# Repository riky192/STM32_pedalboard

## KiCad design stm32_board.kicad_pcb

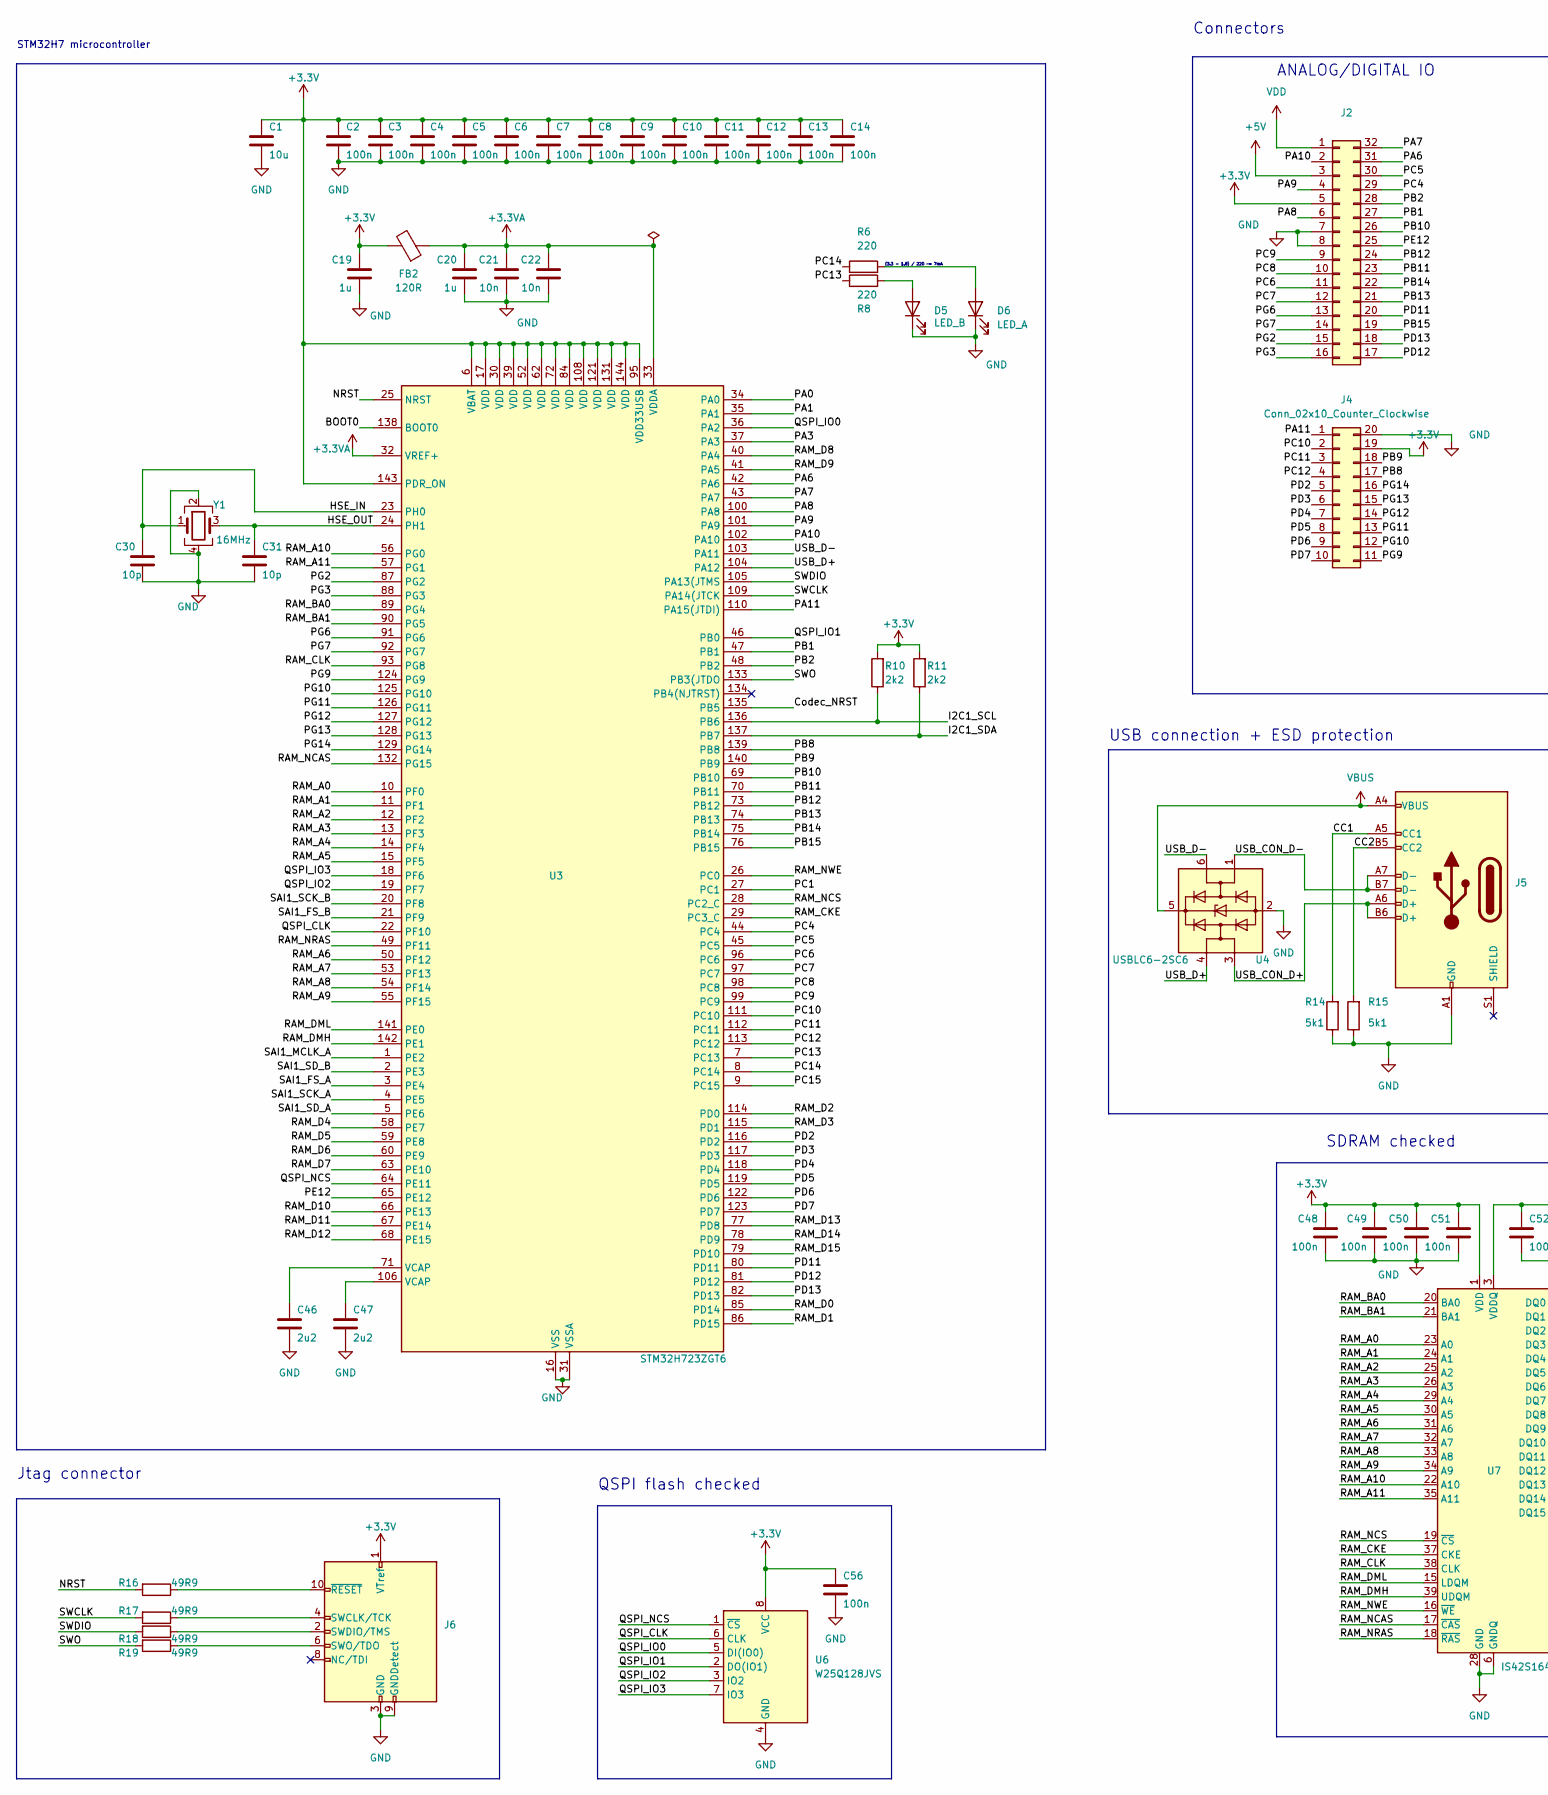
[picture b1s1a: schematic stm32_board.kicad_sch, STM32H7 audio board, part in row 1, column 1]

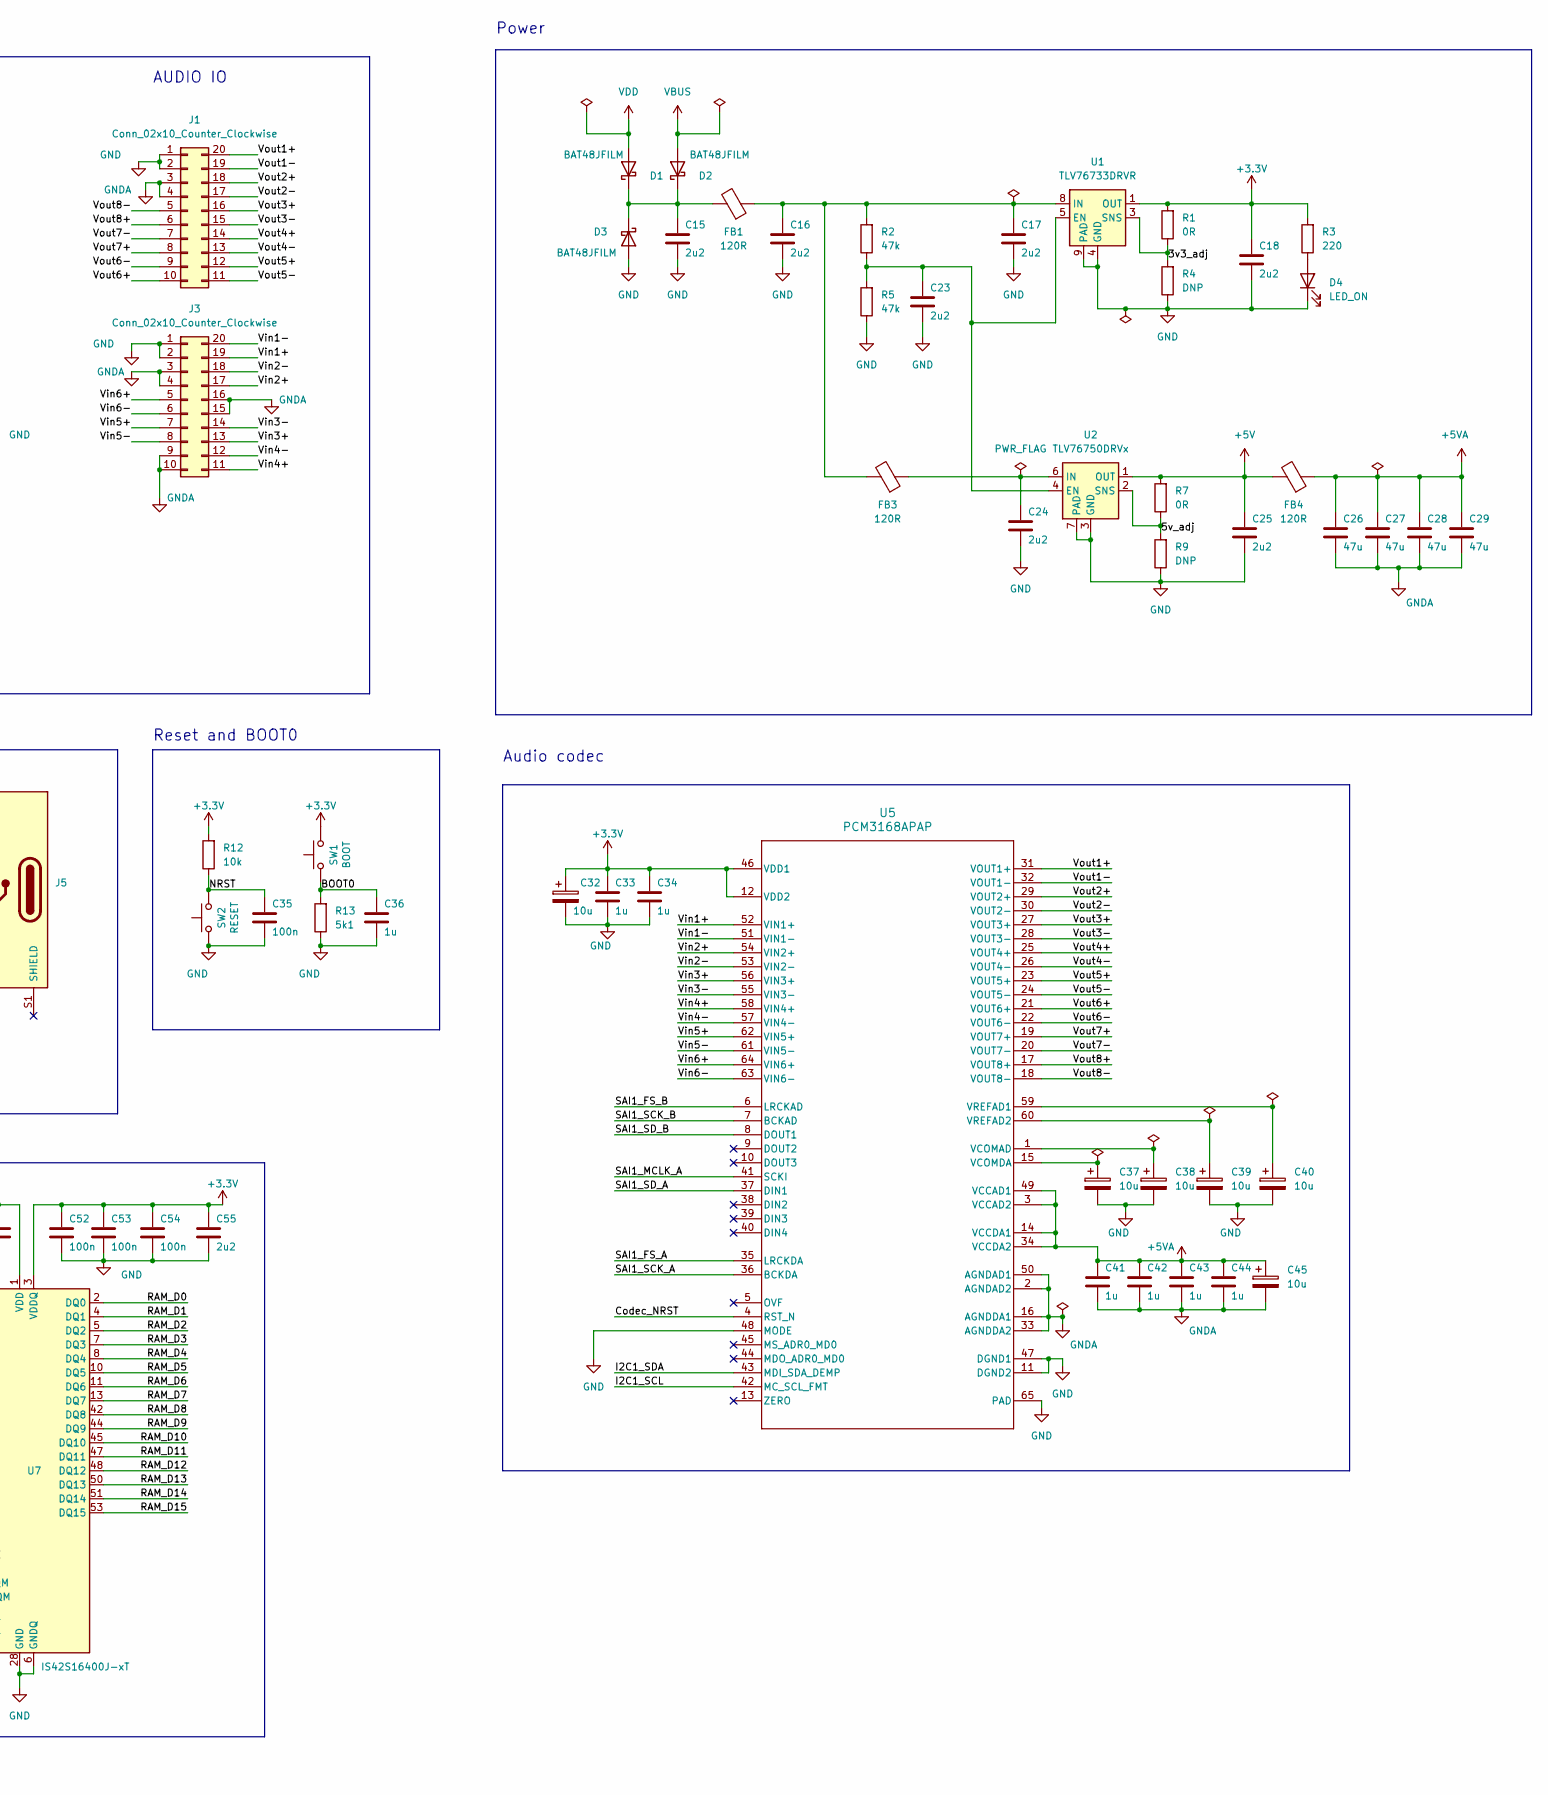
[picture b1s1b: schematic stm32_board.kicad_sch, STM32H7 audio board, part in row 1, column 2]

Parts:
C1, C32, C37, C38, C39, C40, C45: 10u; C_0603_1608Metric_Pad1.08x0.95mm_HandSolder; MANUFACTURER_PART_NUMBER C19702
C2, C3, C4, C5, C6, C7, C8, C9, C10, C11, C12, C13, C14, C35, C48, C49, C50, C51, C52, C53, C54, C56: 100n; C_0603_1608Metric_Pad1.08x0.95mm_HandSolder; MANUFACTURER_PART_NUMBER C14663
C15, C16, C17, C18, C23, C24, C25, C46, C47, C55: 2u2; C_1206_3216Metric_Pad1.33x1.80mm_HandSolder; MANUFACTURER_PART_NUMBER C50254
C19, C20, C33, C34, C36, C41, C42, C43, C44: 1u; C_0603_1608Metric_Pad1.08x0.95mm_HandSolder; MANUFACTURER_PART_NUMBER C15849
C21, C22: 10n; C_0603_1608Metric_Pad1.08x0.95mm_HandSolder; MANUFACTURER_PART_NUMBER C57112
C26, C27, C28, C29: 47u; C_0805_2012Metric_Pad1.18x1.45mm_HandSolder; MANUFACTURER_PART_NUMBER C45783
C30, C31: 10p; C_0603_1608Metric_Pad1.08x0.95mm_HandSolder; MANUFACTURER_PART_NUMBER C1634
D1, D2, D3: BAT48JFILM; D_SOD-323; MANUFACTURER_PART_NUMBER C191023
D4: LED_ON; LED_0805_2012Metric_Pad1.15x1.40mm_HandSolder; MANUFACTURER_PART_NUMBER C2296
D5: LED_B; LED_0805_2012Metric_Pad1.15x1.40mm_HandSolder; MANUFACTURER_PART_NUMBER C5879378
D6: LED_A; LED_0805_2012Metric_Pad1.15x1.40mm_HandSolder; MANUFACTURER_PART_NUMBER C5879378
FB1, FB2, FB3, FB4: 120R; L_0805_2012Metric_Pad1.05x1.20mm_HandSolder; MANUFACTURER_PART_NUMBER C1015
J1, J3, J4: Conn_02x10_Counter_Clockwise; PinHeader_2x10_P2.54mm_Vertical
J2: Conn_02x16_Counter_Clockwise; PinHeader_2x16_P2.54mm_Vertical
J5: USB_C_Receptacle_USB2.0_14P; USB_C_Receptacle_GCT_USB4105-xx-A_16P_TopMnt_Horizontal
J6: Conn_ARM_JTAG_SWD_10; PinHeader_2x05_P1.27mm_Vertical_SMD
R1, R7: 0R; R_0603_1608Metric_Pad0.98x0.95mm_HandSolder; MANUFACTURER_PART_NUMBER C21189
R2, R5: 47k; R_0603_1608Metric_Pad0.98x0.95mm_HandSolder; MANUFACTURER_PART_NUMBER C25819
R3, R6, R8: 220; R_0603_1608Metric_Pad0.98x0.95mm_HandSolder; MANUFACTURER_PART_NUMBER C22962
R4, R9: DNP; R_0603_1608Metric_Pad0.98x0.95mm_HandSolder
R10, R11: 2k2; R_0603_1608Metric_Pad0.98x0.95mm_HandSolder; MANUFACTURER_PART_NUMBER C4190
R12: 10k; R_0603_1608Metric_Pad0.98x0.95mm_HandSolder; MANUFACTURER_PART_NUMBER C25804
R13, R14, R15: 5k1; R_0603_1608Metric_Pad0.98x0.95mm_HandSolder; MANUFACTURER_PART_NUMBER C23186
R16, R17, R18, R19: 49R9; R_0603_1608Metric_Pad0.98x0.95mm_HandSolder; MANUFACTURER_PART_NUMBER C23185
SW1: BOOT; SW_Push_1P1T_XKB_TS-1187A; MANUFACTURER_PART_NUMBER C318884
SW2: RESET; SW_Push_1P1T_XKB_TS-1187A; MANUFACTURER_PART_NUMBER C318884
U1: TLV76733DRVR; VSON-8-1EP_3x3mm_P0.65mm_EP1.65x2.4mm; MANUFACTURER_PART_NUMBER C2848334
U2: TLV76750DRVx; WSON-6-1EP_2x2mm_P0.65mm_EP1x1.6mm_ThermalVias; MANUFACTURER_PART_NUMBER C2860264
U3: STM32H723ZGT6; LQFP-144_20x20mm_P0.5mm; MANUFACTURER_PART_NUMBER C730146
U4: USBLC6-2SC6; SOT-23-6; MANUFACTURER_PART_NUMBER C2687116
U5: PCM3168APAP; PAP0064J_fixed; MANUFACTURER_PART_NUMBER C529289
U6: W25Q128JVS; SOIC-8_5.23x5.23mm_P1.27mm; MANUFACTURER_PART_NUMBER C2613930
U7: IS42S16400J-xT; TSOP-II-54_22.2x10.16mm_P0.8mm; MANUFACTURER_PART_NUMBER C2897490
Y1: 16MHz; Oscillator_SMD_Abracon_ASE-4Pin_3.2x2.5mm_HandSoldering; MANUFACTURER_PART_NUMBER C13738

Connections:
+3.3V: C1.1, C2.1, C3.1, C4.1, C5.1, C6.1, C7.1, C8.1, C9.1, C10.1, C11.1, C12.1, C13.1, C14.1, C18.1, C19.1, C32.1, C33.1, C34.1, C48.1, C49.1, C50.1, C51.1, C52.1, C53.1, C54.1, C55.1, C56.1, FB2.2, J2.5, J4.19, J6.1 (VTref), R1.2, R3.2, R10.2, R11.2, R12.2, SW1.1, U1.1 (OUT), U3.6 (VBAT), U3.17 (VDD), U3.30 (VDD), U3.39 (VDD), U3.52 (VDD), U3.62 (VDD), U3.72 (VDD), U3.84 (VDD), U3.95 (VDD33USB), U3.108 (VDD), U3.121 (VDD), U3.131 (VDD), U3.143 (PDR_ON), U3.144 (VDD), U5.12 (VDD2), U5.46 (VDD1), U6.8 (VCC), U7.1 (VDD), U7.3 (VDDQ), U7.9 (VDDQ), U7.14 (VDD), U7.27 (VDD), U7.43 (VDDQ), U7.49 (VDDQ)
+3.3VA: C20.1, C21.1, C22.1, FB2.1, U3.32 (VREF+), U3.33 (VDDA)
+5V: C25.1, FB4.2, J2.3, R7.2, U2.1 (OUT)
+5VA: C26.1, C27.1, C28.1, C29.1, C41.1, C42.1, C43.1, C44.1, C45.1, FB4.1, U5.3 (VCCAD2), U5.14 (VCCDA1), U5.34 (VCCDA2), U5.49 (VCCAD1)
/3v3_adj: R1.1, R4.2, U1.3 (SNS)
/5v_adj: R7.1, R9.2, U2.2 (SNS)
/BOOT0: C36.1, R13.2, SW1.2, U3.138 (BOOT0)
/CC1: J5.A5 (CC1), R14.2
/CC2: J5.B5 (CC2), R15.2
/Codec_NRST: U3.135 (PB5), U5.4 (RST_N)
/HSE_IN: C30.1, U3.23 (PH0), Y1.1
/HSE_OUT: C31.1, U3.24 (PH1), Y1.3
/I2C1_SCL: R10.1, U3.136 (PB6), U5.42 (MC_SCL_FMT)
/I2C1_SDA: R11.1, U3.137 (PB7), U5.43 (MDI_SDA_DEMP)
/NRST: C35.1, R12.1, R16.2, SW2.1, U3.25 (NRST)
/PA0: U3.34 (PA0)
/PA1: U3.35 (PA1)
/PA3: U3.37 (PA3)
/PA6: J2.31, U3.42 (PA6)
/PA7: J2.32, U3.43 (PA7)
/PA8: J2.6, U3.100 (PA8)
/PA9: J2.4, U3.101 (PA9)
/PA10: J2.2, U3.102 (PA10)
/PA11: J4.1, U3.110 (PA15(JTDI))
/PB1: J2.27, U3.47 (PB1)
/PB2: J2.28, U3.48 (PB2)
/PB8: J4.17, U3.139 (PB8)
/PB9: J4.18, U3.140 (PB9)
/PB10: J2.26, U3.69 (PB10)
/PB11: J2.23, U3.70 (PB11)
/PB12: J2.24, U3.73 (PB12)
/PB13: J2.21, U3.74 (PB13)
/PB14: J2.22, U3.75 (PB14)
/PB15: J2.19, U3.76 (PB15)
/PC1: U3.27 (PC1)
/PC4: J2.29, U3.44 (PC4)
/PC5: J2.30, U3.45 (PC5)
/PC6: J2.11, U3.96 (PC6)
/PC7: J2.12, U3.97 (PC7)
/PC8: J2.10, U3.98 (PC8)
/PC9: J2.9, U3.99 (PC9)
/PC10: J4.2, U3.111 (PC10)
/PC11: J4.3, U3.112 (PC11)
/PC12: J4.4, U3.113 (PC12)
/PC13: R8.1, U3.7 (PC13)
/PC14: R6.1, U3.8 (PC14)
/PC15: U3.9 (PC15)
/PD2: J4.5, U3.116 (PD2)
/PD3: J4.6, U3.117 (PD3)
/PD4: J4.7, U3.118 (PD4)
/PD5: J4.8, U3.119 (PD5)
/PD6: J4.9, U3.122 (PD6)
/PD7: J4.10, U3.123 (PD7)
/PD11: J2.20, U3.80 (PD11)
/PD12: J2.17, U3.81 (PD12)
/PD13: J2.18, U3.82 (PD13)
/PE12: J2.25, U3.65 (PE12)
/PG2: J2.15, U3.87 (PG2)
/PG3: J2.16, U3.88 (PG3)
/PG6: J2.13, U3.91 (PG6)
/PG7: J2.14, U3.92 (PG7)
/PG9: J4.11, U3.124 (PG9)
/PG10: J4.12, U3.125 (PG10)
/PG11: J4.13, U3.126 (PG11)
/PG12: J4.14, U3.127 (PG12)
/PG13: J4.15, U3.128 (PG13)
/PG14: J4.16, U3.129 (PG14)
/QSPI_CLK: U3.22 (PF10), U6.6 (CLK)
/QSPI_IO0: U3.36 (PA2), U6.5 (DI(IO0))
/QSPI_IO1: U3.46 (PB0), U6.2 (DO(IO1))
/QSPI_IO2: U3.19 (PF7), U6.3 (IO2)
/QSPI_IO3: U3.18 (PF6), U6.7 (IO3)
/QSPI_NCS: U3.64 (PE11), U6.1 (~CS)
/RAM_A0: U3.10 (PF0), U7.23 (A0)
/RAM_A1: U3.11 (PF1), U7.24 (A1)
/RAM_A2: U3.12 (PF2), U7.25 (A2)
/RAM_A3: U3.13 (PF3), U7.26 (A3)
/RAM_A4: U3.14 (PF4), U7.29 (A4)
/RAM_A5: U3.15 (PF5), U7.30 (A5)
/RAM_A6: U3.50 (PF12), U7.31 (A6)
/RAM_A7: U3.53 (PF13), U7.32 (A7)
/RAM_A8: U3.54 (PF14), U7.33 (A8)
/RAM_A9: U3.55 (PF15), U7.34 (A9)
/RAM_A10: U3.56 (PG0), U7.22 (A10)
/RAM_A11: U3.57 (PG1), U7.35 (A11)
/RAM_BA0: U3.89 (PG4), U7.20 (BA0)
/RAM_BA1: U3.90 (PG5), U7.21 (BA1)
/RAM_CKE: U3.29 (PC3_C), U7.37 (CKE)
/RAM_CLK: U3.93 (PG8), U7.38 (CLK)
/RAM_D0: U3.85 (PD14), U7.2 (DQ0)
/RAM_D1: U3.86 (PD15), U7.4 (DQ1)
/RAM_D2: U3.114 (PD0), U7.5 (DQ2)
/RAM_D3: U3.115 (PD1), U7.7 (DQ3)
/RAM_D4: U3.58 (PE7), U7.8 (DQ4)
/RAM_D5: U3.59 (PE8), U7.10 (DQ5)
/RAM_D6: U3.60 (PE9), U7.11 (DQ6)
/RAM_D7: U3.63 (PE10), U7.13 (DQ7)
/RAM_D8: U3.40 (PA4), U7.42 (DQ8)
/RAM_D9: U3.41 (PA5), U7.44 (DQ9)
/RAM_D10: U3.66 (PE13), U7.45 (DQ10)
/RAM_D11: U3.67 (PE14), U7.47 (DQ11)
/RAM_D12: U3.68 (PE15), U7.48 (DQ12)
/RAM_D13: U3.77 (PD8), U7.50 (DQ13)
/RAM_D14: U3.78 (PD9), U7.51 (DQ14)
/RAM_D15: U3.79 (PD10), U7.53 (DQ15)
/RAM_DMH: U3.142 (PE1), U7.39 (UDQM)
/RAM_DML: U3.141 (PE0), U7.15 (LDQM)
/RAM_NCAS: U3.132 (PG15), U7.17 (~CAS)
/RAM_NCS: U3.28 (PC2_C), U7.19 (~CS)
/RAM_NRAS: U3.49 (PF11), U7.18 (~RAS)
/RAM_NWE: U3.26 (PC0), U7.16 (~WE)
/SAI1_FS_A: U3.3 (PE4), U5.35 (LRCKDA)
/SAI1_FS_B: U3.21 (PF9), U5.6 (LRCKAD)
/SAI1_MCLK_A: U3.1 (PE2), U5.41 (SCKI)
/SAI1_SCK_A: U3.4 (PE5), U5.36 (BCKDA)
/SAI1_SCK_B: U3.20 (PF8), U5.7 (BCKAD)
/SAI1_SD_A: U3.5 (PE6), U5.37 (DIN1)
/SAI1_SD_B: U3.2 (PE3), U5.8 (DOUT1)
/SWCLK: R17.2, U3.109 (PA14(JTCK)
/SWDIO: R18.2, U3.105 (PA13(JTMS)
/SWO: R19.2, U3.133 (PB3(JTDO)
/USB_CON_D+: J5.A6 (D+), J5.B6 (D+), U4.3 (I/O2)
/USB_CON_D-: J5.A7 (D-), J5.B7 (D-), U4.1 (I/O1)
/USB_D+: U3.104 (PA12), U4.4 (I/O2)
/USB_D-: U3.103 (PA11), U4.6 (I/O1)
/Vin1+: J3.19, U5.52 (VIN1+)
/Vin1-: J3.20, U5.51 (VIN1-)
/Vin2+: J3.17, U5.54 (VIN2+)
/Vin2-: J3.18, U5.53 (VIN2-)
/Vin3+: J3.13, U5.56 (VIN3+)
/Vin3-: J3.14, U5.55 (VIN3-)
/Vin4+: J3.11, U5.58 (VIN4+)
/Vin4-: J3.12, U5.57 (VIN4-)
/Vin5+: J3.7, U5.62 (VIN5+)
/Vin5-: J3.8, U5.61 (VIN5-)
/Vin6+: J3.5, U5.64 (VIN6+)
/Vin6-: J3.6, U5.63 (VIN6-)
/Vout1+: J1.20, U5.31 (VOUT1+)
/Vout1-: J1.19, U5.32 (VOUT1-)
/Vout2+: J1.18, U5.29 (VOUT2+)
/Vout2-: J1.17, U5.30 (VOUT2-)
/Vout3+: J1.16, U5.27 (VOUT3+)
/Vout3-: J1.15, U5.28 (VOUT3-)
/Vout4+: J1.14, U5.25 (VOUT4+)
/Vout4-: J1.13, U5.26 (VOUT4-)
/Vout5+: J1.12, U5.23 (VOUT5+)
/Vout5-: J1.11, U5.24 (VOUT5-)
/Vout6+: J1.10, U5.21 (VOUT6+)
/Vout6-: J1.9, U5.22 (VOUT6-)
/Vout7+: J1.8, U5.19 (VOUT7+)
/Vout7-: J1.7, U5.20 (VOUT7-)
/Vout8+: J1.6, U5.17 (VOUT8+)
/Vout8-: J1.5, U5.18 (VOUT8-)
GND: C1.2, C2.2, C3.2, C4.2, C5.2, C6.2, C7.2, C8.2, C9.2, C10.2, C11.2, C12.2, C13.2, C14.2, C15.2, C16.2, C17.2, C18.2, C19.2, C20.2, C21.2, C22.2, C23.2, C24.2, C25.2, C30.2, C31.2, C32.2, C33.2, C34.2, C35.2, C36.2, C37.2, C38.2, C39.2, C40.2, C46.2, C47.2, C48.2, C49.2, C50.2, C51.2, C52.2, C53.2, C54.2, C55.2, C56.2, D3.2 (A), D4.1 (K), D5.1 (K), D6.1 (K), J1.1, J1.2, J2.7, J2.8, J3.1, J3.2, J4.20, J5.A1 (GND), J5.A12 (GND), J5.B1 (GND), J5.B12 (GND), J6.3 (GND), J6.5 (GND), J6.9 (GNDDetect), R4.1, R5.1, R9.1, R13.1, R14.1, R15.1, SW2.2, U1.4 (GND), U1.6 (GND), U1.9 (PAD), U2.3 (GND), U2.5 (GND), U2.7 (PAD), U3.16 (VSS), U3.31 (VSSA), U3.38 (VSS), U3.51 (VSS), U3.61 (VSS), U3.83 (VSS), U3.94 (VSS), U3.107 (VSS), U3.120 (VSS), U3.130 (VSS), U4.2 (GND), U5.11 (DGND2), U5.47 (DGND1), U5.48 (MODE), U5.65 (PAD), U6.4 (GND), U7.6 (GNDQ), U7.12 (GNDQ), U7.28 (GND), U7.41 (GND), U7.46 (GNDQ), U7.52 (GNDQ), U7.54 (GND), Y1.2, Y1.4
GNDA: C26.2, C27.2, C28.2, C29.2, C41.2, C42.2, C43.2, C44.2, C45.2, J1.3, J1.4, J3.3, J3.4, J3.9, J3.10, J3.15, J3.16, U5.2 (AGNDAD2), U5.16 (AGNDDA1), U5.33 (AGNDDA2), U5.50 (AGNDAD1)
unnamed: C46.1, U3.71 (VCAP)
unnamed: C47.1, U3.106 (VCAP)
unnamed: C15.1, D1.1 (K), D2.1 (K), D3.1 (K), FB1.2
unnamed: D4.2 (A), R3.1
unnamed: D5.2 (A), R8.2
unnamed: D6.2 (A), R6.2
unnamed: J6.4 (SWCLK/TCK), R17.1
unnamed: J6.2 (SWDIO/TMS), R18.1
unnamed: J6.6 (SWO/TDO), R19.1
unnamed: J6.10 (~RESET), R16.1
unnamed: C23.1, R2.1, R5.2, U1.5 (EN), U2.4 (EN)
unnamed: C16.1, C17.1, FB1.1, FB3.2, R2.2, U1.8 (IN)
unnamed: C24.1, FB3.1, U2.6 (IN)
unnamed: C38.1, U5.1 (VCOMAD)
unnamed: C37.1, U5.15 (VCOMDA)
unnamed: C40.1, U5.59 (VREFAD1)
unnamed: C39.1, U5.60 (VREFAD2)
VBUS: D2.2 (A), J5.A4 (VBUS), J5.A9 (VBUS), J5.B4 (VBUS), J5.B9 (VBUS), U4.5 (VBUS)
VDD: D1.2 (A), J2.1

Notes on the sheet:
Power
Jtag connector
(3.3 - 1.8) / 220 ~= 7mA
SDRAM checked
AUDIO IO
STM32H7 microcontroller
Connectors
QSPI flash checked
ANALOG/DIGITAL IO
USB connection + ESD protection
Audio codec
Reset and BOOT0

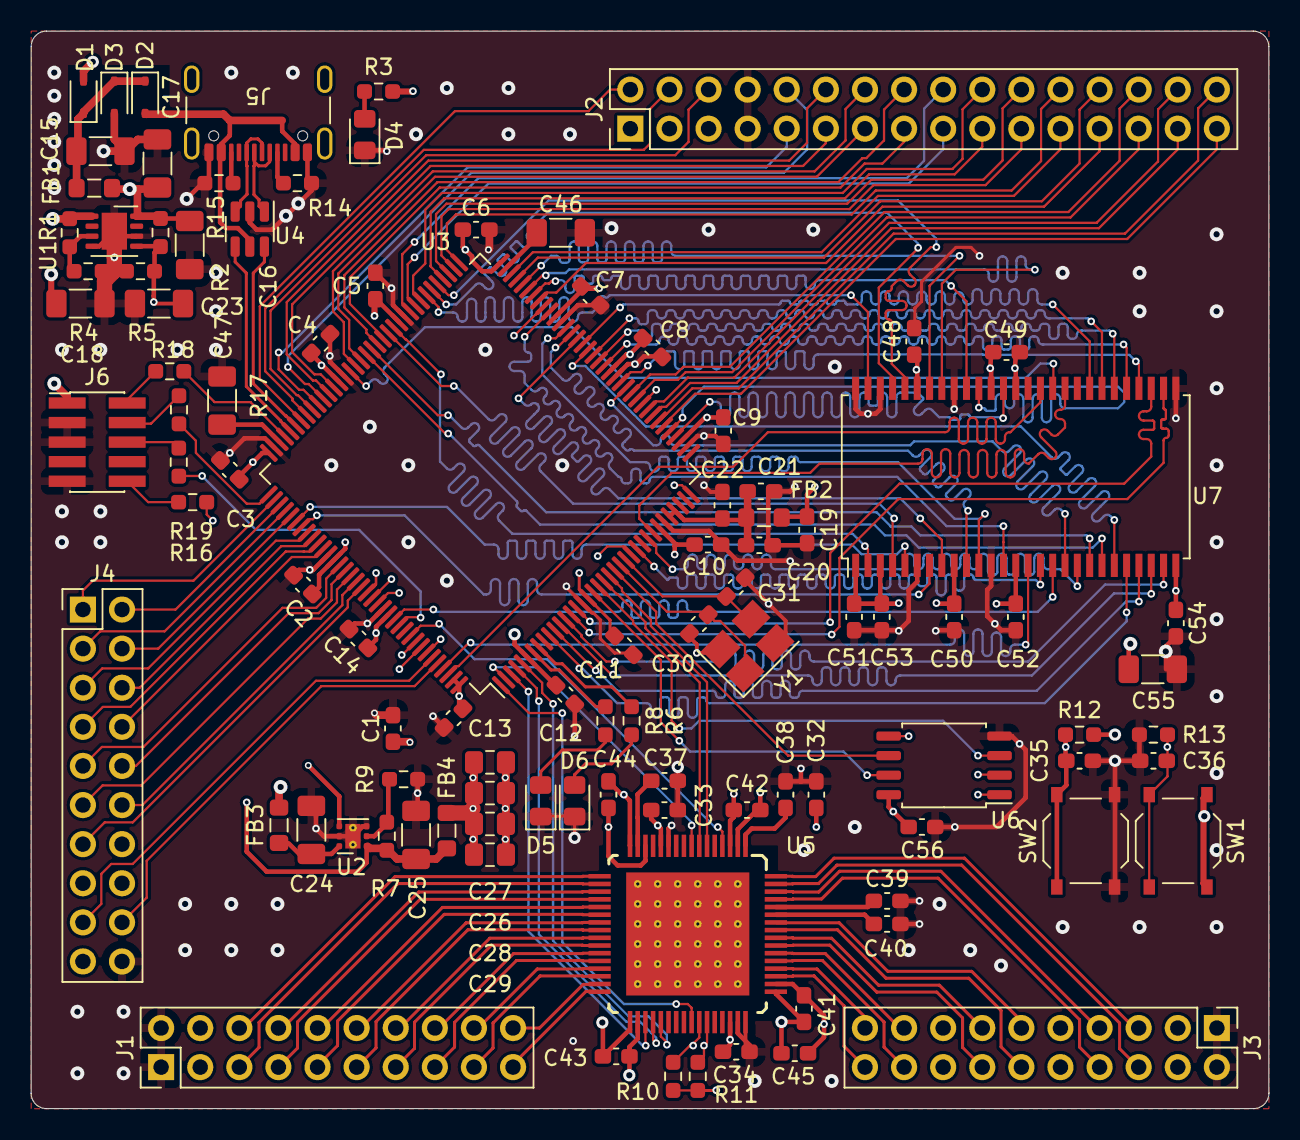
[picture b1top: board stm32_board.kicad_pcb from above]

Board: 4 copper layers, 80.4 x 70.0 mm, 101 parts (0 on the bottom side), 169 nets.

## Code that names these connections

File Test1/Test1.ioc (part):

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Mcu.Name=STM32H723ZGTx
Mcu.Package=LQFP144
Mcu.UserName=STM32H723ZGTx
PA13(JTMS/SWDIO).Mode=Trace_Asynchronous_SW
PA13(JTMS/SWDIO).Signal=DEBUG_JTMS-SWDIO
PA14(JTCK/SWCLK).Mode=Trace_Asynchronous_SW
PA14(JTCK/SWCLK).Signal=DEBUG_JTCK-SWCLK
PB3(JTDO/TRACESWO).Mode=Trace_Asynchronous_SW
PB3(JTDO/TRACESWO).Signal=DEBUG_JTDO-SWO
PB6.Mode=I2C
PB6.Signal=I2C1_SCL
PB7.Mode=I2C
PB7.Signal=I2C1_SDA
PC13.Signal=GPIO_Output
PC14-OSC32_IN.Signal=GPIO_Output
PC8.Signal=GPIO_Output
PE2.Mode=SAI_A_MasterWithClock
PE2.Signal=SAI1_MCLK_A
PE3.Mode=SAI_B_AsyncSlave
PE3.Signal=SAI1_SD_B
PE4.Mode=SAI_A_MasterWithClock
PE4.Signal=SAI1_FS_A
PE5.Mode=SAI_A_MasterWithClock
PE5.Signal=SAI1_SCK_A
PE6.Mode=SAI_A_MasterWithClock
PE6.Signal=SAI1_SD_A
PF8.Mode=SAI_B_AsyncSlave
PF8.Signal=SAI1_SCK_B
PF9.Mode=SAI_B_AsyncSlave
PF9.Signal=SAI1_FS_B
PH0-OSC_IN.Mode=HSE-External-Oscillator
PH0-OSC_IN.Signal=RCC_OSC_IN
PH1-OSC_OUT.Mode=HSE-External-Oscillator
PH1-OSC_OUT.Signal=RCC_OSC_OUT
RCC.HSE_VALUE=16000000
RCC.SYSCLKFreq_VALUE=550000000
RCC.SYSCLKSource=RCC_SYSCLKSOURCE_PLLCLK
board=custom

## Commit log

2024-04-29 Rename IS42SM32160E_6BLI.zip to Kicad/IS42SM32160E_6BLI.zip
2024-04-29 Rename fp-info-cache to Kicad/fp-info-cache
2024-04-29 Rename stm32_board.kicad_pro to Kicad/stm32_board.kicad_pro
2024-04-29 Rename sym-lib-table to Kicad/sym-lib-table
2024-04-29 Rename stm32_board.kicad_sch to Kicad/stm32_board.kicad_sch
2024-04-29 Rename stm32_board.kicad_pcb to Kicad/stm32_board.kicad_pcb
2024-04-29 Rename stm32_board.kicad_prl to Kicad/stm32_board.kicad_prl
2024-04-29 Rename fp-lib-table to Kicad/fp-lib-table
2024-05-25 First trial
2024-05-25 Petit test :)
2024-05-25 Chat gpt framework
